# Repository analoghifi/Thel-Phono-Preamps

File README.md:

### "High-End":  
* predecessor models:
  * "VX-5021P" 1996 ➔ https://web.archive.org/web/20160323223326/http://thel-audioworld.de/test/test.htm#VX5021
  * "Phono-M" 2006 ➔ https://web.archive.org/web/20070626215210/http://www.thel-audioworld.de/module/phono/phono-M.htm
  * "Phono-HQ" 12/2017 ➔ https://web.archive.org/web/20180203013342/http://www.thel-audioworld.de/module/phono/phono-hq.htm
* <b>\"<a href="/hardware/beautiful%20noise">Beautiful-Noise</a>\" 09/2018</b>  
Stereo module / 2 channels galvanically isolated / single ended inputs, single ended outputs  
two-stage passive RIAA-filter  
adjustable gain (6-step) / input resistance changeable (by soldering) / input capacity changeable (by soldering)  
➔ https://web.archive.org/web/20190110103246/http://www.thel-audioworld.de/module/phono/Phonovorstufe-B.htm

### "Ultra-High-End":  
* predecessor models:
  * "Majestic" 1998 ➔ https://web.archive.org/web/20160323223326/http://thel-audioworld.de/test/test.htm#Majestic
  * "VP2000" 2002 ➔ https://web.archive.org/web/20020410123225/http://thel-audioworld.de/module/phono/phono.htm
  * "Phono-X" 2007-2017 ➔ https://web.archive.org/web/20070312044356/http://www.thel-audioworld.de/module/phono/phono.htm
  * "Phono HQX" 12/2017 ➔ https://web.archive.org/web/20180203012402/http://www.thel-audioworld.de/module/phono/phono-hqx.htm
* <b>\"<a href="/hardware/sound%20of%20silence">Sound of Silence</a>\" 09/2018</b>  
Mono module / true\* fully symmetrical / balanced input -> balanced filter stages -> balanced output  
\*(no ground reference at any point in the audio signal chain)  
two-stage passive balanced RIAA-filter  
adjustable input resistor (16-step) / adjustable input capacity (16-step) / adjustable gain (16-step)  
➔ https://web.archive.org/web/20190109011016/http://www.thel-audioworld.de/module/phono/Phonovorstufe-S.htm  

----  
calculation of the R C Values for the passive 2-step (inverse) RIAA filter:  
https://docs.google.com/spreadsheets/d/1qcIyMvDhxXAbTDFzf901tkU7BbxNvI2y0nLj_5HbEa4/edit?usp=sharing  

----  
#### "Beautiful-Noise":  

.  
  
#### "Sound of Silence":  

----  
### Kicad projects in this repo:  
* ["Sound of Silence"](https://github.com/analoghifi/Thel-Phono-Preamps/tree/main/hardware/sound%20of%20silence/KiCad/original) | state: initial release v1.01 | like the original, 1-layer, THT
* ["Sound of Silence WIMA Edition"](https://github.com/analoghifi/Thel-Phono-Preamps/tree/main/hardware/sound%20of%20silence/KiCad/WIMA-Edition) | state: initial release v1.01 | all WIMA Caps | like the original, 1-layer, THT
* ["Beautiful Noise"](https://github.com/analoghifi/Thel-Phono-Preamps/tree/main/hardware/beautiful%20noise/KiCad/original) | state: coming soon... | like the original, 1-layer, THT

----

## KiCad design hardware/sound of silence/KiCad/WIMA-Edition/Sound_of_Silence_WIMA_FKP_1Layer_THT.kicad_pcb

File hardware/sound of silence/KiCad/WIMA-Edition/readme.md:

### This special edition exclusively uses the highly valued WIMA polypropylene capacitors throughout  
(FKP = highest quality film/foil types for the passive RIAA filter and the input (load-) Capacitors)  
* C101,C102,C201..C214 = WIMA FKP2 33nF 63V 1% (tanδ = 0.0005)  
* C3,C4,C6 = WIMA FKP2 100V 1% (tanδ = 0.0005)
* C5,C7 = WIMA FKP2 47pF 1000V 2.5% (tanδ = 0.0005)
* C8,C9,C12,C13,C14,C15 = WIMA MKP2 63V 5% (tanδ = 0.0005)  
  
see -> [List of used capacitors for the "WIMA-Edition"](https://github.com/analoghifi/Thel-Phono-Preamps/blob/main/hardware/sound%20of%20silence/KiCad/WIMA-Edition/Capacitor_BOM.md)  
  
#### this is not the original Thel PCB but it's very like\* the original with the following exceptions:  
* different board dimensions original: 155mm x 60mm -> this PCB: 155mm x 64mm  
* different mounting hole spacing original: 148mm x 53mm -> this PCB: 148mm x 57mm  
* "C2" is 462nF (paralleled 14x33nF Wima FKP2 1%) 
* "C1" is 66nF (paralleled 2x33nF Wima FKP2 1%)
* "C1" is in a different location on the board  
* using WIMA FKP2 (instead of ceramics) for the input (load-) Capacitors as well C3 ..C7  
* more massive ground and power supply PCB tracks  
* additional GND track unterneath U1 and U2 
  
\*(same schematic / same 1-layer\** layout THT / same THT components in the same places on the board)  
\**(strictly speaking, this KiCad PCB is a two-layer PCB with plated-through holes, but you can also (let) produce it as a classic 1-layer PCB with non-plated holes if you wish, since all the tracks are on the bottom side only)  

----  

### remarks:  
#### R6,R7:  
one can use 23,7kΩ or 24kΩ instead  
or use 2x47kΩ in parallel each  
when using MM-Systems (choosing R<sub>in</sub> = 47kΩ [SW2=0]):  
for lower noise one may use low-TCR-types (25ppm/°C or lower) if available  
e.g. Vishay "[CMF Industrial](https://www.mouser.com/c/passive-components/resistors/film-resistors/metal-film-resistors-through-hole/?m=Vishay&series=CMF%20Industrial)" series  
or Vishay [PTF series](https://www.mouser.de/c/passive-components/resistors/film-resistors/metal-film-resistors-through-hole/?m=Vishay&series=PTF) (even lower TCR)  
or Tyco (TE Connectivity) type "[YR1B23k7CC](https://www.mouser.com/ProductDetail/TE-Connectivity-Holsworthy/YR1B23K7CC?qs=n4i9pByFsMSkJXItUSDcPw%3D%3D)" (23.7kΩ / 0.1% / 15ppm/°C) [from the Tyco ["YR1-series" (R-series)](https://www.mouser.com/c/passive-components/resistors/film-resistors/metal-film-resistors-through-hole/?m=TE%20Connectivity&series=R)]  
#### U1,U2,U3,U4,U5:  
instead of [LME49720](https://www2.mouser.com/ProductDetail/Texas-Instruments/LME49720NA-NOPB?qs=7lkVKPoqpbYtIqwyg5iDaA%3D%3D) you can use [LM4562](https://www2.mouser.com/ProductDetail/Texas-Instruments/LM4562NA-NOPB?qs=QbsRYf82W3Gc2w4DLq%252BZjw%3D%3D) (both Texas Instruments),  
these two are 100% identical (even regarding their inner guts).
  
----  
  
these are KiCad 6.x projects  
see how to get the proper 3D-Models from here: https://github.com/analoghifi/KiCad-3D-Models
  
----  
  
use kicanvas.org to view this KiCad project in your browser:  
https://kicanvas.org/?github=https%3A%2F%2Fgithub.com%2Fanaloghifi%2FThel-Phono-Preamps%2Ftree%2Fmain%2Fhardware%2Fsound%2520of%2520silence%2FKiCad%2FWIMA-Edition

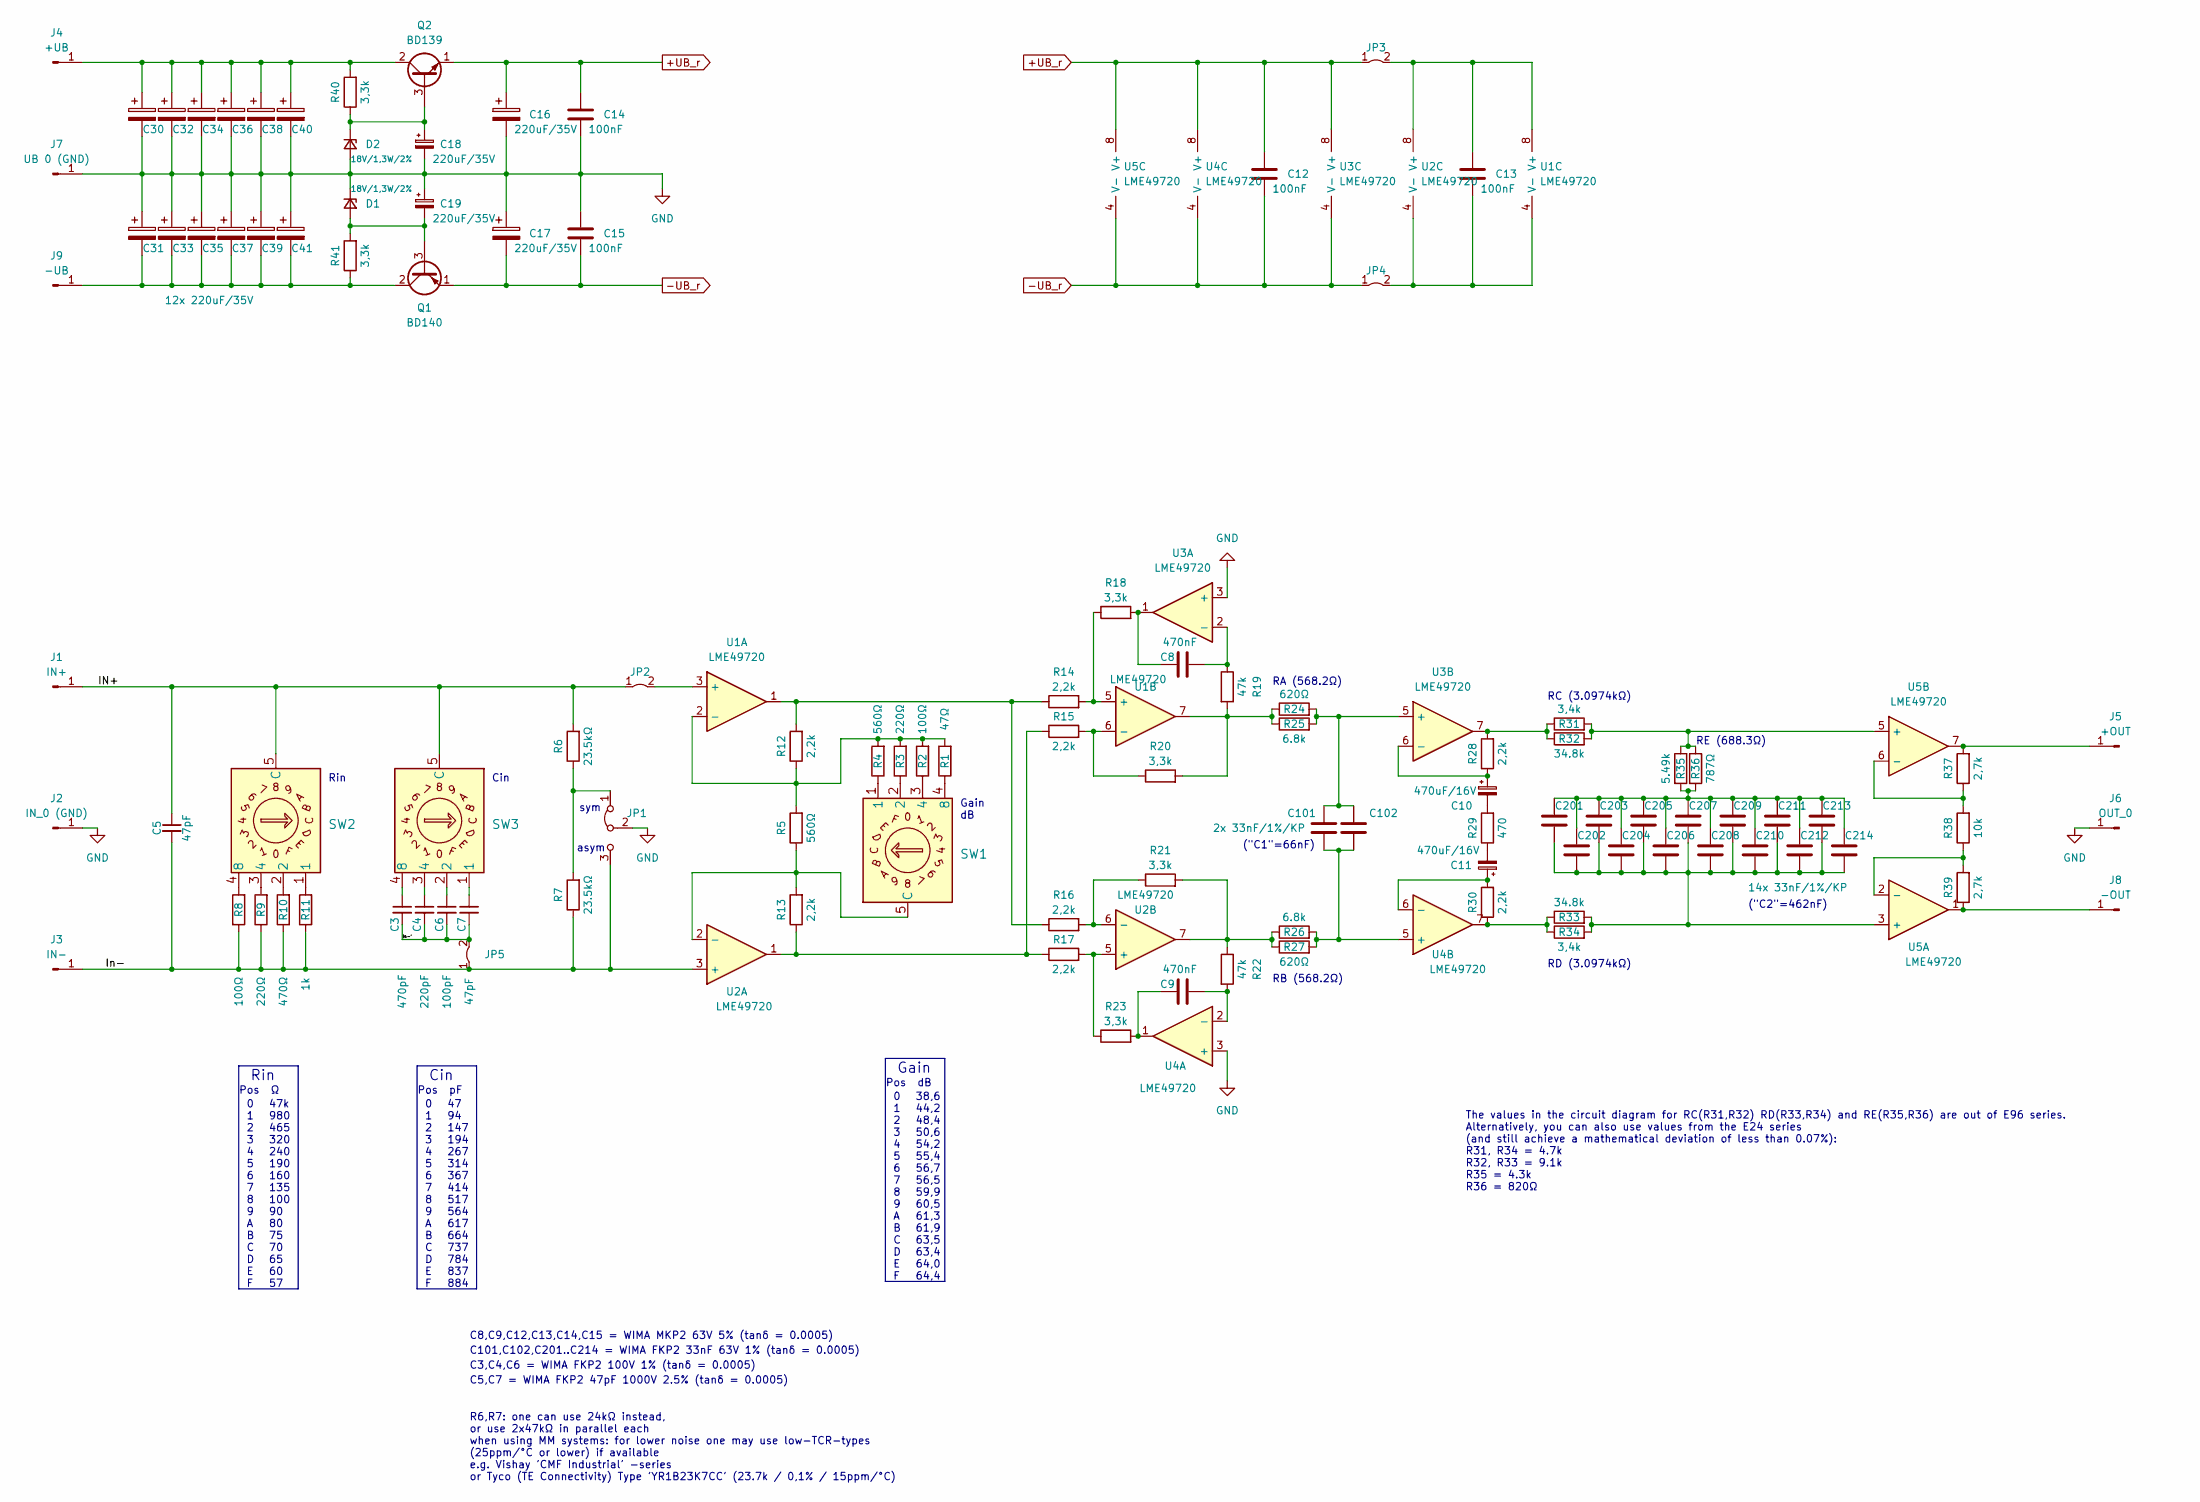
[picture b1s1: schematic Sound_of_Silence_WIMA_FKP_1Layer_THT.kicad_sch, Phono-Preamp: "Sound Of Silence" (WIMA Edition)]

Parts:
C3: 470pF; C_Rect_L7.2mm_W4.5mm_P5.00mm_FKS2_FKP2_MKS2_MKP2
C4: 220pF; C_Rect_L7.2mm_W4.5mm_P5.00mm_FKS2_FKP2_MKS2_MKP2
C5, C7: 47pF; C_Rect_L7.2mm_W4.5mm_P5.00mm_FKS2_FKP2_MKS2_MKP2
C6: 100pF; C_Rect_L7.2mm_W4.5mm_P5.00mm_FKS2_FKP2_MKS2_MKP2
C8, C9: 470nF; C_Rect_L7.2mm_W8.5mm_P5.00mm_FKP2_FKP2_MKS2_MKP2
C10, C11: 470uF/16V; CP_Radial_Black_D8.2mm_H12.0mm_P3.50mm_minimal_silk
C12, C13, C14, C15: 100nF; C_Rect_L7.2mm_W5.0mm_P5.00mm_FKS2_FKP2_MKS2_MKP2
C16, C17, C18, C19, C30, C32, C33, C34, C35, C36, C37, C38, C39, C40, C41: 220uF/35V; CP_Radial_Black_D8.2mm_H12.0mm_P3.50mm_minimal_silk
C31: 12x 220uF/35V; CP_Radial_Black_D8.2mm_H12.0mm_P3.50mm_minimal_silk
C101, C202, C203, C204, C205, C206, C207, C208, C209, C210, C211, C212, C213, C214: 33nF/1%/KP; C_Rect_L7.2mm_W8.5mm_P5.00mm_FKP2_FKP2_MKS2_MKP2
C102: 2x 33nF/1%/KP; C_Rect_L7.2mm_W8.5mm_P5.00mm_FKP2_FKP2_MKS2_MKP2
C201: 14x 33nF/1%/KP; C_Rect_L7.2mm_W8.5mm_P5.00mm_FKP2_FKP2_MKS2_MKP2
D1, D2: 18V/1,3W/2%; D_DO-41_SOD81_medium_P9.33mm_Horiz_minSilk
J1: IN+; Loet_Pin_D1.5mm_L14.0mm
J2: IN_0 (GND); Loet_Pin_D1.5mm_L14.0mm
J3: IN-; Loet_Pin_D1.5mm_L14.0mm
J4: +UB; Loet_Pin_D1.5mm_L14.0mm
J5: +OUT; Loet_Pin_D1.5mm_L14.0mm
J6: OUT_0; Loet_Pin_D1.5mm_L14.0mm
J7: UB 0 (GND); Loet_Pin_D1.5mm_L14.0mm
J8: -OUT; Loet_Pin_D1.5mm_L14.0mm
J9: -UB; Loet_Pin_D1.5mm_L14.0mm
JP1: Jumper_3_Bridged12; PinHeader_1x03_P2.54mm_Vertical
JP2, JP3, JP4, JP5: Jumper_2_Bridged; Drahtbruecke_10.16mm
Q1: BD140; TO-126-3_Vertical
Q2: BD139; TO-126-3_Vertical
R1: 47Ω; R_Axial_DIN0207_L6.3mm_D2.5mm_P10.16mm_Horizontal_minSilk
R2, R8: 100Ω; R_Axial_DIN0207_L6.3mm_D2.5mm_P10.16mm_Horizontal_minSilk
R3, R9: 220Ω; R_Axial_DIN0207_L6.3mm_D2.5mm_P10.16mm_Horizontal_minSilk
R4, R5: 560Ω; R_Axial_DIN0207_L6.3mm_D2.5mm_P10.16mm_Horizontal_minSilk
R6, R7: 23.5kΩ; R_Axial_DIN0207_L6.3mm_D2.5mm_P10.16mm_Horizontal_minSilk
R10: 470Ω; R_Axial_DIN0207_L6.3mm_D2.5mm_P10.16mm_Horizontal_minSilk
R11: 1k; R_Axial_DIN0207_L6.3mm_D2.5mm_P10.16mm_Horizontal_minSilk
R12, R13, R14, R15, R16, R17, R28, R30: 2,2k; R_Axial_DIN0207_L6.3mm_D2.5mm_P10.16mm_Horizontal_minSilk
R18, R20, R21, R23, R40, R41: 3,3k; R_Axial_DIN0207_L6.3mm_D2.5mm_P10.16mm_Horizontal_minSilk
R19, R22: 47k; R_Axial_DIN0207_L6.3mm_D2.5mm_P10.16mm_Horizontal_minSilk
R24, R27: 620Ω; R_Axial_DIN0207_L6.3mm_D2.5mm_P10.16mm_Horizontal_minSilk
R25, R26: 6.8k; R_Axial_DIN0207_L6.3mm_D2.5mm_P10.16mm_Horizontal_minSilk
R29: 470; R_Axial_DIN0207_L6.3mm_D2.5mm_P10.16mm_Horizontal_minSilk
R31, R34: 3,4k; R_Axial_DIN0207_L6.3mm_D2.5mm_P10.16mm_Horizontal_minSilk
R32, R33: 34.8k; R_Axial_DIN0207_L6.3mm_D2.5mm_P10.16mm_Horizontal_minSilk
R35: 5.49k; R_Axial_DIN0207_L6.3mm_D2.5mm_P10.16mm_Horizontal_minSilk
R36: 787Ω; R_Axial_DIN0207_L6.3mm_D2.5mm_P10.16mm_Horizontal_minSilk
R37, R39: 2,7k; R_Axial_DIN0207_L6.3mm_D2.5mm_P10.16mm_Horizontal_minSilk
R38: 10k; R_Axial_DIN0207_L6.3mm_D2.5mm_P10.16mm_Horizontal_minSilk
SW1, SW2, SW3: DRS4010; DRS_3016_4010_horiz_and_vert
U1, U2, U3, U4, U5: LME49720; DIP-8_W7.62mm

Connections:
+UB_r: C12.1, C14.1, C16.1, JP3.1 (A), Q2.1 (E), U3.8 (V+), U4.8 (V+), U5.8 (V+)
-UB_r: C12.2, C15.2, C17.2, JP4.1 (A), Q1.1 (E), U3.4 (V-), U4.4 (V-), U5.4 (V-)
/IN+: C5.1, J1.1, JP2.1 (A), R6.2, SW2.5 (C), SW3.5 (C)
/In-: C5.2, J3.1, JP1.3 (B), JP5.1 (A), R7.1, R8.1, R9.1, R10.1, R11.1, U2.3 (+)
/In-': C3.2, C4.2, C6.2, C7.2, JP5.2 (B)
GND: C14.2, C15.1, C16.2, C17.1, C18.2, C19.1, C30.2, C31.1, C32.2, C33.1, C34.2, C35.1, C36.2, C37.1, C38.2, C39.1, C40.2, C41.1, D1.1 (K), D2.2 (A), J2.1, J6.1, J7.1, JP1.2 (C), U3.3 (+), U4.3 (+)
unnamed: C3.1, SW3.4 (8)
unnamed: C4.1, SW3.3 (4)
unnamed: C6.1, SW3.2
unnamed: C7.1, SW3.1
unnamed: C8.1, R18.2, U3.1
unnamed: C8.2, R19.1, U3.2 (-)
unnamed: C9.1, R23.2, U4.1
unnamed: C9.2, R22.2, U4.2 (-)
unnamed: C10.1, R28.1, U3.6 (-)
unnamed: C10.2, R29.2
unnamed: C11.1, R30.2, U4.6 (-)
unnamed: C11.2, R29.1
unnamed: C13.1, JP3.2 (B), U1.8 (V+), U2.8 (V+)
unnamed: C13.2, JP4.2 (B), U1.4 (V-), U2.4 (V-)
unnamed: C18.1, D2.1 (K), Q2.3 (B), R40.1
unnamed: C19.2, D1.2 (A), Q1.3 (B), R41.2
unnamed: C30.1, C32.1, C34.1, C36.1, C38.1, C40.1, J4.1, Q2.2 (C), R40.2
unnamed: C31.2, C33.2, C35.2, C37.2, C39.2, C41.2, J9.1, Q1.2 (C), R41.1
unnamed: C101.1, C102.1, R24.2, R25.2, U3.5 (+)
unnamed: C101.2, C102.2, R26.2, R27.2, U4.5 (+)
unnamed: C201.1, C202.1, C203.1, C204.1, C205.1, C206.1, C207.1, C208.1, C209.1, C210.1, C211.1, C212.1, C213.1, C214.1, R35.2, R36.2
unnamed: C201.2, C202.2, C203.2, C204.2, C205.2, C206.2, C207.2, C208.2, C209.2, C210.2, C211.2, C212.2, C213.2, C214.2, R33.2, R34.2, U5.3 (+)
unnamed: J5.1, R37.2, U5.7
unnamed: J8.1, R39.1, U5.1
unnamed: JP1.1 (A), R6.1, R7.2
unnamed: JP2.2 (B), U1.3 (+)
unnamed: R1.1, SW1.4 (8)
unnamed: R1.2, R2.2, R3.2, R4.2, R5.2, R12.1, U1.2 (-)
unnamed: R2.1, SW1.3 (4)
unnamed: R3.1, SW1.2
unnamed: R4.1, SW1.1
unnamed: R8.2, SW2.4 (8)
unnamed: R9.2, SW2.3 (4)
unnamed: R10.2, SW2.2
unnamed: R11.2, SW2.1
unnamed: R12.2, R14.1, R16.1, U1.1
unnamed: R13.1, R15.1, R17.1, U2.1
unnamed: R5.1, R13.2, SW1.5 (C), U2.2 (-)
unnamed: R14.2, R18.1, U1.5 (+)
unnamed: R15.2, R20.1, U1.6 (-)
unnamed: R16.2, R21.1, U2.6 (-)
unnamed: R17.2, R23.1, U2.5 (+)
unnamed: R19.2, R20.2, R24.1, R25.1, U1.7
unnamed: R21.2, R22.1, R26.1, R27.1, U2.7
unnamed: R28.2, R31.1, R32.1, U3.7
unnamed: R30.1, R33.1, R34.1, U4.7
unnamed: R31.2, R32.2, R35.1, R36.1, U5.5 (+)
unnamed: R37.1, R38.2, U5.6 (-)
unnamed: R38.1, R39.2, U5.2 (-)

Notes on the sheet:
RE (688.3Ω)
Cin
RD (3.0974kΩ)
0 1 2 3 4 5 6 7 8 9 A B C D E F
asym
C3,C4,C6 = WIMA FKP2 100V 1% (tanδ = 0.0005)
("C1"=66nF)
Pos Ω
RB (568.2Ω)
Pos dB
47k 980 465 320 240 190 160 135 100 90 80 75 70 65 60 57
R6,R7: one can use 24kΩ instead, or use 2x47kΩ in parallel each when using MM systems: for lower noise one may use low-TCR-types (25ppm/°C or lower) if available e.g. Vishay 'CMF Industrial' -series or Tyco (TE Connectivity) Type 'YR1B23K7CC' (23.7k / 0,1% / 15ppm/°C)
Gain
Rin
sym
The values in the circuit diagram for RC(R31,R32) RD(R33,R34) and RE(R35,R36) are out of E96 series. Alternatively, you can also use values from the E24 series (and still achieve a mathematical deviation of less than 0.07%): R31, R34 = 4.7k R32, R33 = 9.1k R35 = 4.3k R36 = 820Ω
C8,C9,C12,C13,C14,C15 = WIMA MKP2 63V 5% (tanδ = 0.0005)
Gain dB
C5,C7 = WIMA FKP2 47pF 1000V 2.5% (tanδ = 0.0005)
47 94 147 194 267 314 367 414 517 564 617 664 737 784 837 884
C101,C102,C201..C214 = WIMA FKP2 33nF 63V 1% (tanδ = 0.0005)
38,6 44,2 48,4 50,6 54,2 55,4 56,7 56,5 59,9 60,5 61,3 61,9 63,5 63,4 64,0 64,4
RA (568.2Ω)
RC (3.0974kΩ)
Pos pF
("C2"=462nF)

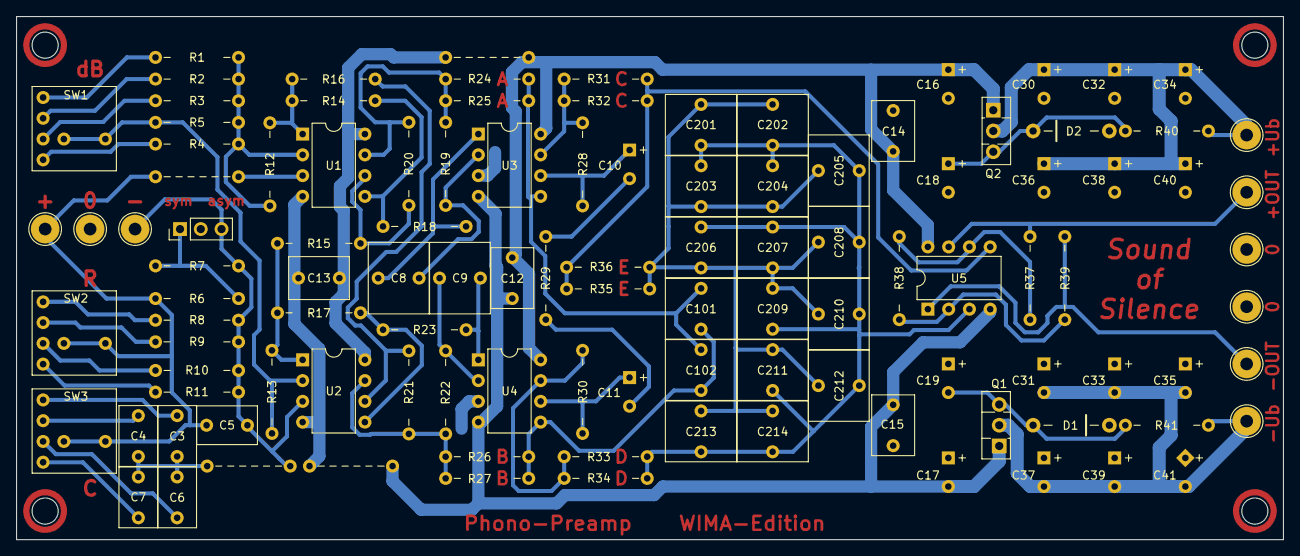
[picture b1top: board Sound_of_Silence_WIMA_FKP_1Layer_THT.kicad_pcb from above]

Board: 2 copper layers, 155.0 x 64.0 mm, 112 parts (0 on the bottom side), 55 nets.
